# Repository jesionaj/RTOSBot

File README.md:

# RTOSBot
A small robot that uses my [HobbyOS](https://github.com/jesionaj/HobbyOS/) code. A video describing this project can be found [here](https://www.youtube.com/watch?v=qPOtINk6i20).

Parallax's Board of Education shield is the base of the robot, which includes the frame, motors, and encoders. For the brains, I laid out my own PCB with a PIC32MX250F128B chip, which you can find in the hardware folder.

The robot is driven using Wiimote Nunchuck. While it drives, the LCD on top displays encoder data and joystick position, which is also written to an SD card. After the driving is finished, that data can be copied off of the SD card (see below). An included Python script reads this data and reconstructs the robot's path using dead reckoning.

### Build Instructions
1. Run `git clone https://github.com/jesionaj/HobbyOS.git` in the RTOSBot folder.  
2. Open the RTOSBot project in MPLAB and hit build. That's it!

### Dead Reckoning  
The dead reckoning script requires Python 2.7, pygame 1.9.2, and numpy. Data is recorded on the SD card starting at address 0x400.  
1. Open the `python` folder and copy the data off the robot's SD card using (for OSX at least): `sudo dd bs=512 skip=2 if=/dev/rdisk# of=sdcard_data count=20`, where # is the SD card's disk number. Sample data is provided.  
2. Run `python InterpretFile.py sdcard_data`  
3. Before removing the SD card, run `sudo dd bs=512 seek=2 if=/dev/zero of=/dev/rdisk# count=20` to wipe out the old run.

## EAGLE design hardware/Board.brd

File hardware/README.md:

Included here are the Eagle project files for the PCB, as well as the gerber output.

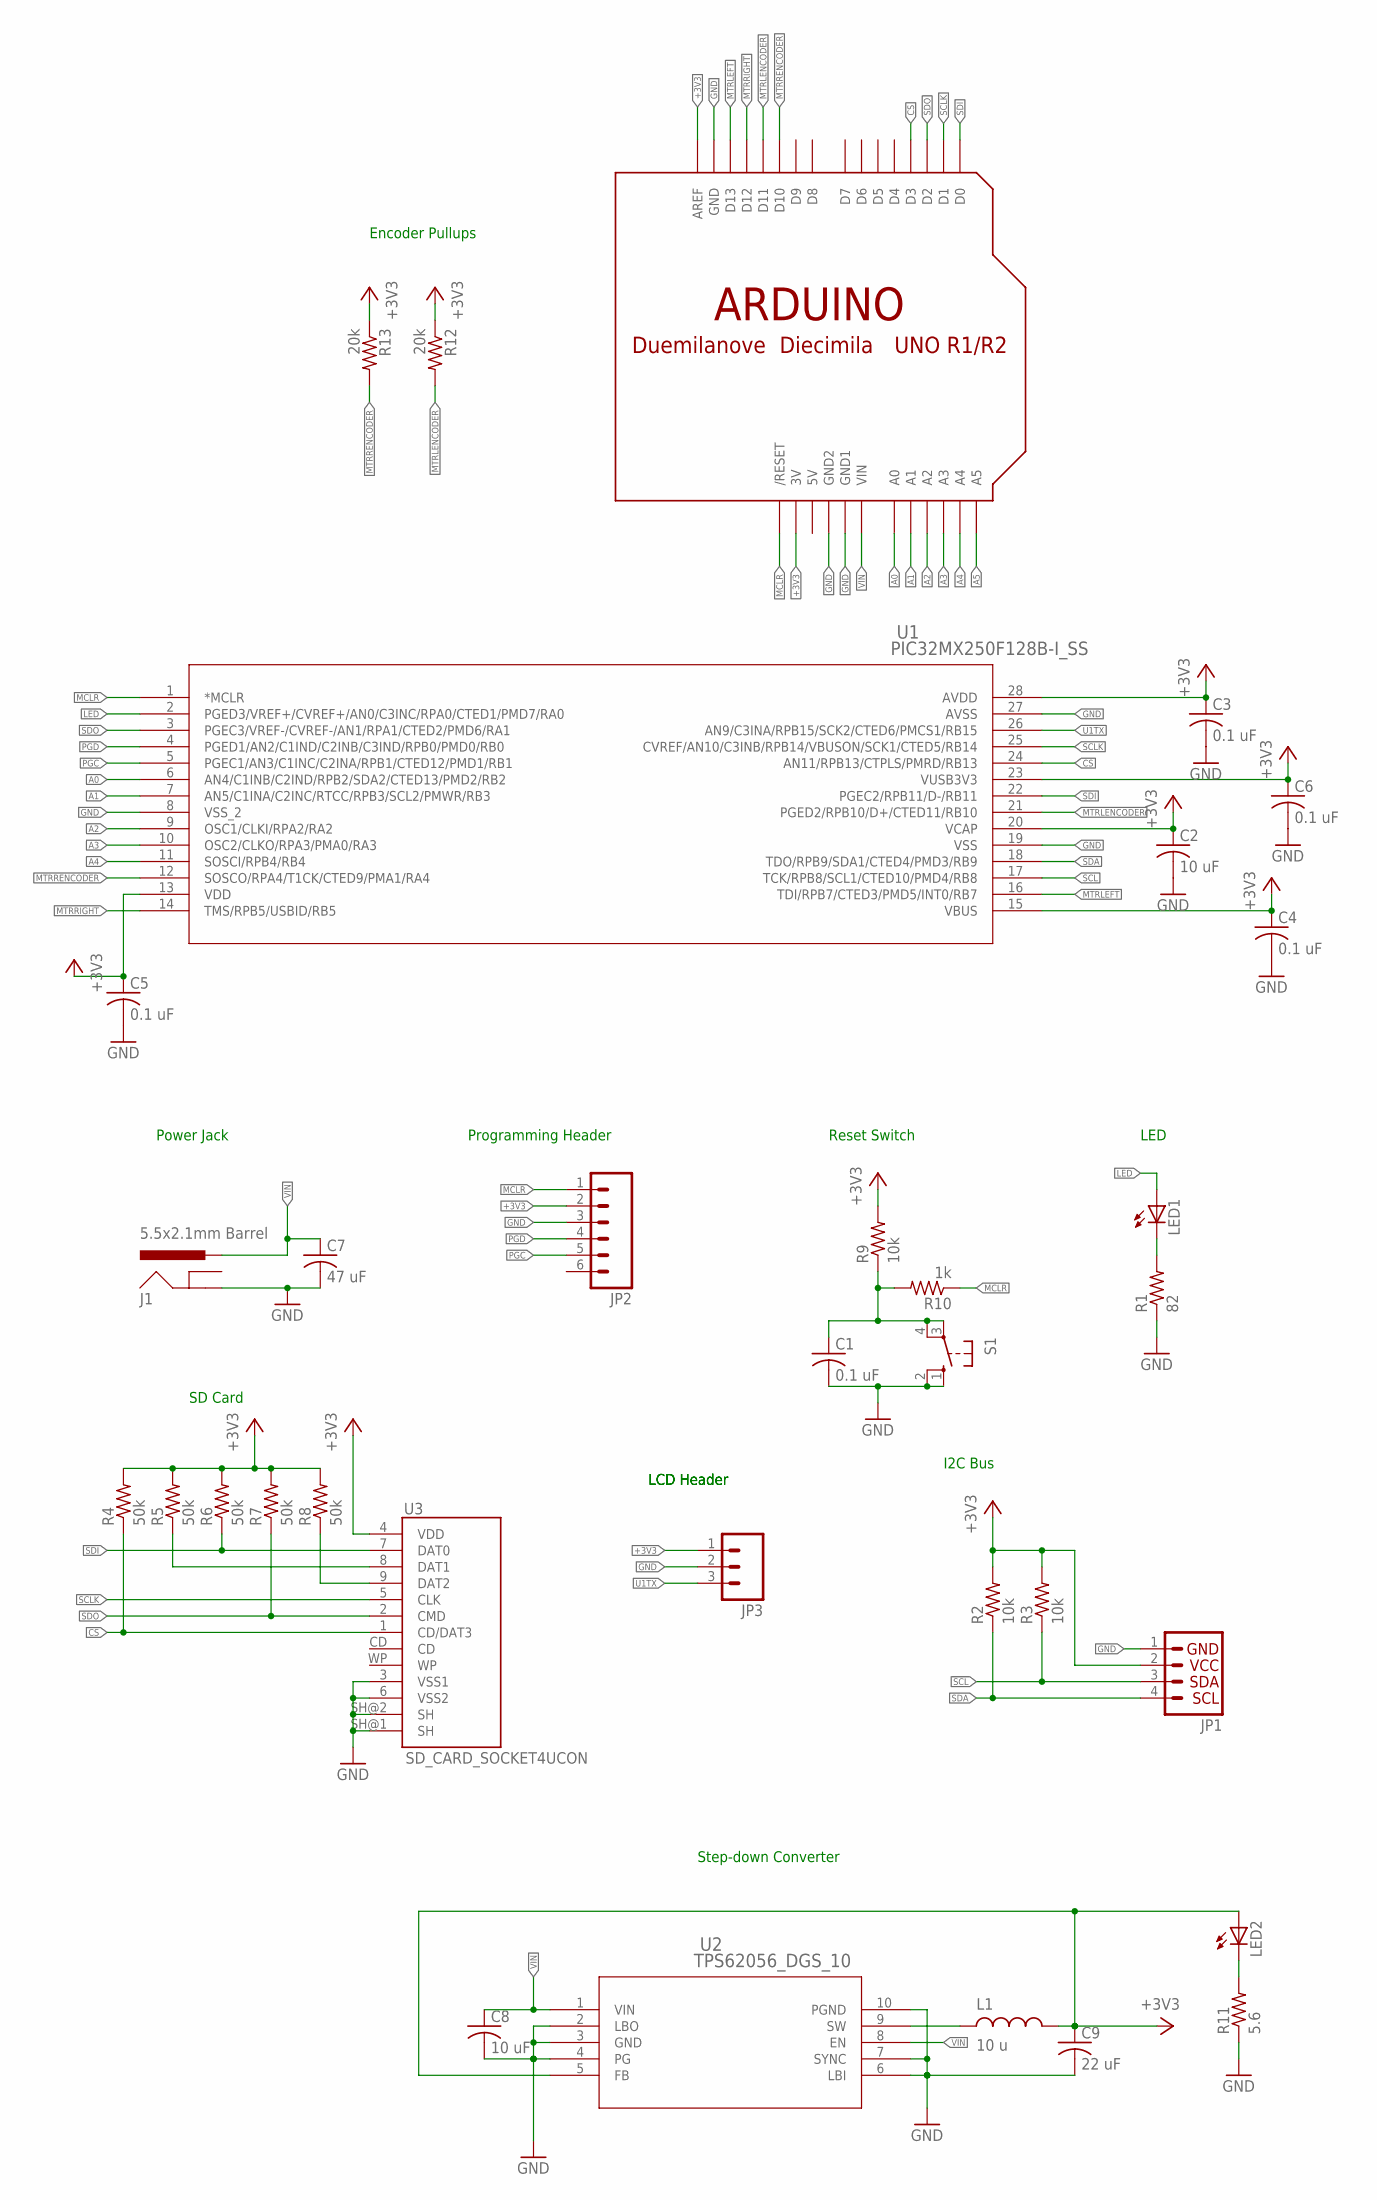
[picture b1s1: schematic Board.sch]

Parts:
C1, C3, C4, C5, C6: 0.1 uF; C0805
C2, C8: 10 uF; C0805
C7: 47 uF; C0805
C9: 22 uF; C0805
J1: 5.5x2.1mm Barrel; POWER_JACK_SMD
JP1: I2C_STANDARD; 1X04
JP2: M06SILK_FEMALE_PTH; 1X06
JP3: M03PTH; 1X03
L1: 10 u; SLF7032T-100M1R4-2PF
LED1, LED2: LEDCHIPLED_1206; CHIPLED_1206
R1: 82; R1210W
R2, R3, R9: 10k; R0805W
R4, R5, R6, R7, R8: 50k; R0805W
R10: 1k; R0805W
R11: 5.6; R1210W
R12, R13: 20k; R0805W
S1: 10-XX; B3F-10XX
U1: PIC32MX250F128B-I_SS; SSOP28_MC
U2: TPS62056_DGS_10; DGS10
U3: SD_CARD_SOCKET4UCON; SDCARD_4UCONN
U$1: ARDUINO-NOHOLE

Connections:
5V: U$1.5V
+3V3: C2.1, C3.1, C4.1, C5.1, C6.1, C9.1, JP1.2, JP2.2, JP3.1, L1.P$2, LED2.A, R2.2, R3.2, R4.2, R5.2, R6.2, R7.2, R8.2, R9.2, R12.1, R13.1, U1.13 (VDD), U1.15 (VBUS), U1.20 (VCAP), U1.23 (VUSB3V3), U1.28 (AVDD), U2.5 (FB), U3.4 (VDD), U$1.3V, U$1.AREF
A0: U1.6 (AN4/C1INB/C2IND/RPB2/SDA2/CTED13/PMD2/R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), U$1.A0
A1: U1.7 (AN5/C1INA/C2INC/RTCC/RPB3/SCL2/PMWR/RB3), U$1.A1
A2: U1.9 (OSC1/CLKI/RPA2/RA2), U$1.A2
A3: U1.10 (OSC2/CLKO/RPA3/PMA0/RA3), U$1.A3
A4: U1.11 (SOSCI/RPB4/RB4), U$1.A4
A5: U$1.A5
CS: R4.1, U1.24 (AN11/RPB13/CTPLS/PMRD/RB13), U3.1 (CD/DAT3), U$1.D3
GND: C1.2, C2.2, C3.2, C4.2, C5.2, C6.2, C7.2, C8.2, C9.2, J1.P$4 (GND), JP1.1, JP2.3, JP3.2, R1.1, R11.1, S1.1 (S), S1.2 (S1), U1.8 (VSS_2), U1.19 (VSS), U1.27 (AVSS), U2.2 (LBO), U2.3 (GND), U2.4 (PG), U2.6 (LBI), U2.7 (SYNC), U2.10 (PGND), U3.3 (VSS1), U3.6 (VSS2), U3.SH@1 (SH), U3.SH@2 (SH), U$1.GND, U$1.GND1, U$1.GND2
LED: LED1.A, U1.2 (PGED3/VREF+/CVREF+/AN0/C3INC/RPA0/CTED1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)
MCLR: JP2.1, R10.1, U1.1 (*MCLR), U$1.RESET (/RESET)
MTRLEFT: U1.16 (TDI/RPB7/CTED3/PMD5/INT0/RB7), U$1.D13
MTRLENCODER: R12.2, U1.21 (PGED2/RPB10/D+/CTED11/RB10), U$1.D11
MTRRENCODER: R13.2, U1.12 (SOSCO/RPA4/T1CK/CTED9/PMA1/RA4), U$1.D10
MTRRIGHT: U1.14 (TMS/RPB5/USBID/RB5), U$1.D12
unnamed: LED1.C, R1.2
unnamed: R8.1, U3.9 (DAT2)
unnamed: R5.1, U3.8 (DAT1)
unnamed: C1.1, R9.1, R10.2, S1.3, S1.4 (P1)
unnamed: LED2.C, R11.2
unnamed: L1.P$1, U2.9 (SW)
PGC: JP2.5, U1.5 (PGEC1/AN3/C1INC/C2INA/RPB1/CTED12/PMD1/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)
PGD: JP2.4, U1.4 (PGED1/AN2/C1IND/C2INB/C3IND/RPB0/PMD0/R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)
SCL: JP1.3, R3.1, U1.17 (TCK/RPB8/SCL1/CTED10/PMD4/RB8)
SCLK: U1.25 (CVREF/AN10/C3INB/RPB14/VBUSON/SCK1/CTED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), U3.5 (CLK), U$1.D1
SDA: JP1.4, R2.1, U1.18 (TDO/RPB9/SDA1/CTED4/PMD3/RB9)
SDI: R6.1, U1.22 (PGEC2/RPB11/D-/RB11), U3.7 (DAT0), U$1.D0
SDO: R7.1, U1.3 (PGEC3/VREF-/CVREF-/AN1/RPA1/CTED2/PMD6/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), U3.2 (CMD), U$1.D2
U1TX: JP3.3, U1.26 (AN9/C3INA/RPB15/SCK2/CTED6/PMCS1/RB15)
VIN: C7.1, C8.1, J1.VIN0 (PWR), U2.1 (VIN), U2.8 (EN), U$1.VIN

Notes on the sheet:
Reset Switch
SD Card
Programming Header
Power Jack
LCD Header
LED
I2C Bus
Step-down Converter
Encoder Pullups

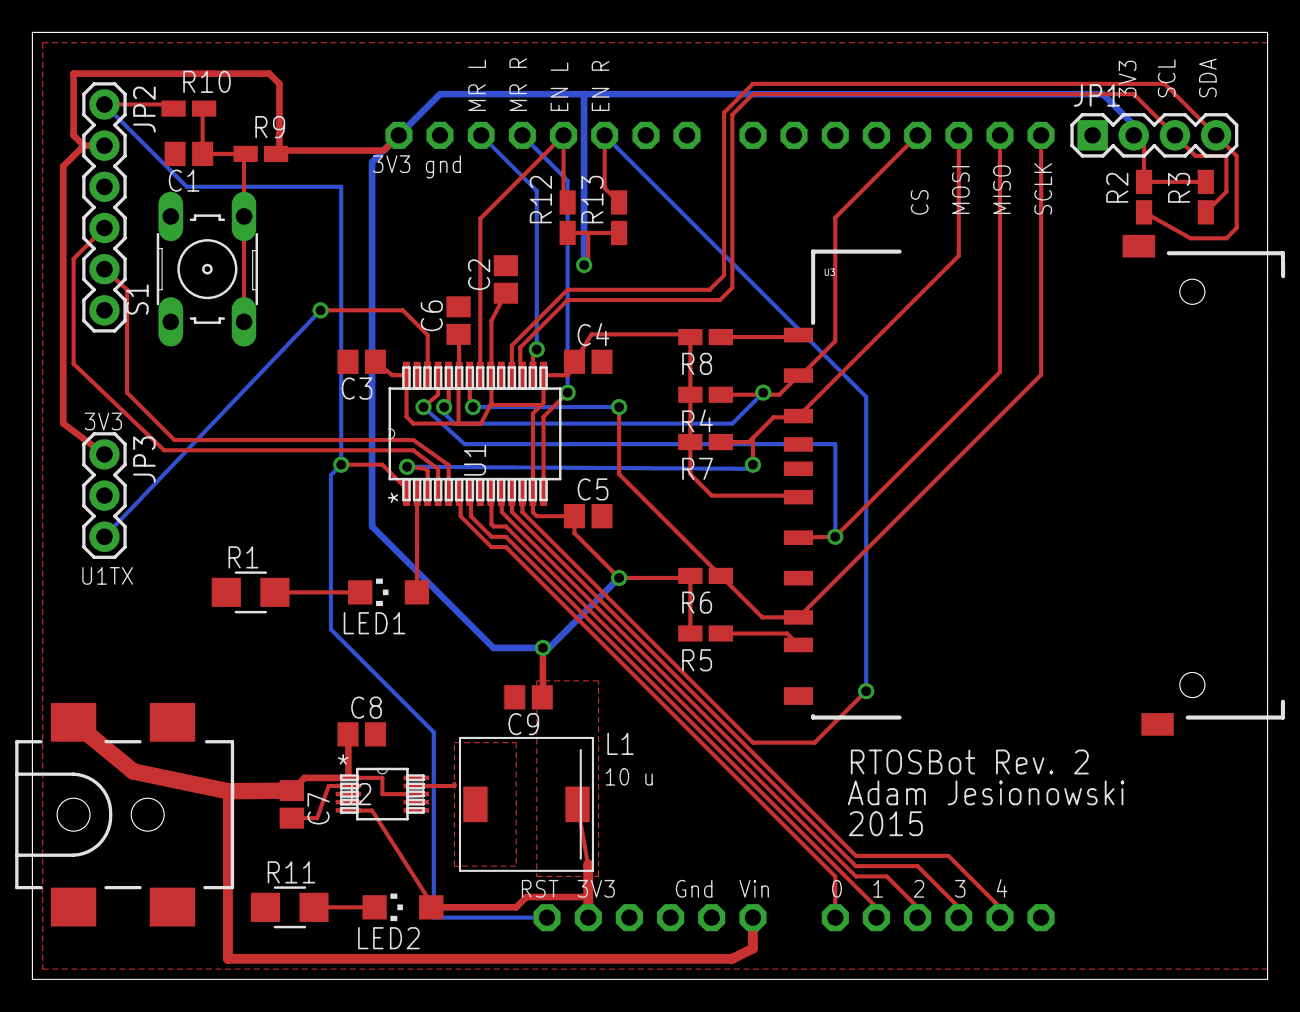
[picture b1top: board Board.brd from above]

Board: 2 copper layers, 76.2 x 58.4 mm, 34 parts (0 on the bottom side), 29 nets.

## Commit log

2015-02-27 Initial commit.

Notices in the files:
parts and their libraries:
SparkFun-Connectors: Licensing: Creative Commons ShareAlike 4.0 International - https://creativecommons.org/licenses/by-sa/4.0
